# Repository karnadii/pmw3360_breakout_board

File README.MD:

# PMW3360 Minimal Breakout Board
my version of PMW3360 breakout board from https://github.com/jfedor2/pmw3360-breakout/, I have a little space to put the breakout in so that's why the shape is weird. only work for 3.3v, Not tested yet.

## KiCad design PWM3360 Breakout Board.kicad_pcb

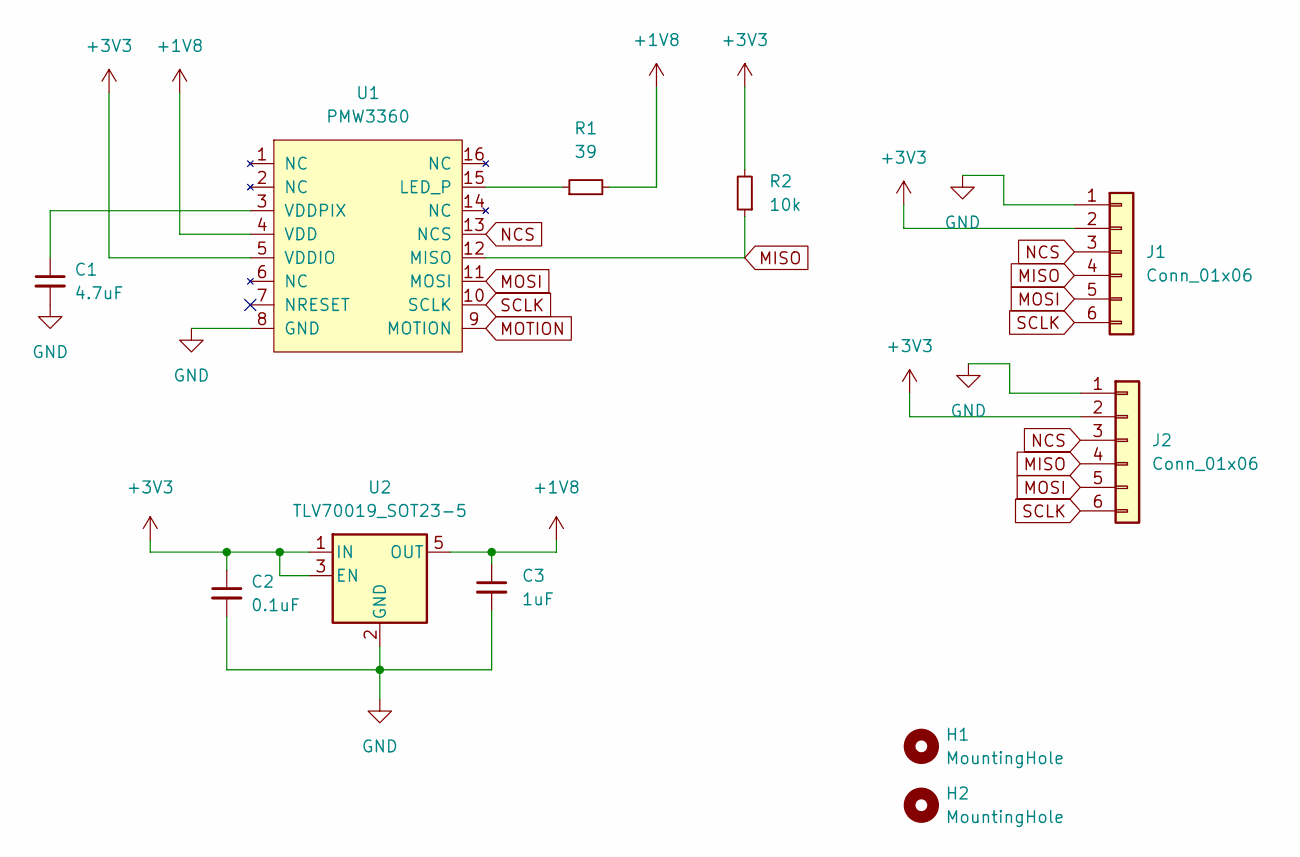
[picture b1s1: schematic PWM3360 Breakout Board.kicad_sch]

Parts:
C1: 4.7uF; C_0603_1608Metric_Pad1.08x0.95mm_HandSolder; LCSC C19666
C2: 0.1uF; C_0603_1608Metric_Pad1.08x0.95mm_HandSolder; LCSC C14663
C3: 1uF; C_0603_1608Metric_Pad1.08x0.95mm_HandSolder; LCSC C15849
H1, H2: MountingHole; MountingHole_2.2mm_M2_DIN965_Pad
J1: Conn_01x06; JST_SH_SM06B-SRSS-TB_1x06-1MP_P1.00mm_Horizontal
J2: Conn_01x06; PinHeader_1x06_P2.54mm_Vertical
R1: 39; R_0603_1608Metric_Pad0.98x0.95mm_HandSolder; LCSC C365424
R2: 10k; R_0603_1608Metric_Pad0.98x0.95mm_HandSolder; LCSC C25804
U1: PMW3360
U2: TLV70019_SOT23-5; SOT-23-5; LCSC C146366

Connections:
+1V8: C3.1, R1.2, U1.4 (VDD), U2.5 (OUT)
+3V3: C2.1, J1.2, J2.2, R2.2, U1.5 (VDDIO), U2.1 (IN), U2.3 (EN)
GND: C1.2, C2.2, C3.2, J1.1, J2.1, U1.8 (GND), U2.2 (GND)
MISO: J1.4, J2.4, R2.1, U1.12 (MISO)
MOSI: J1.5, J2.5, U1.11 (MOSI)
MOTION: U1.9 (MOTION)
NCS: J1.3, J2.3, U1.13 (NCS)
unnamed: C1.1, U1.3 (VDDPIX)
unnamed: R1.1, U1.15 (LED_P)
SCLK: J1.6, J2.6, U1.10 (SCLK)

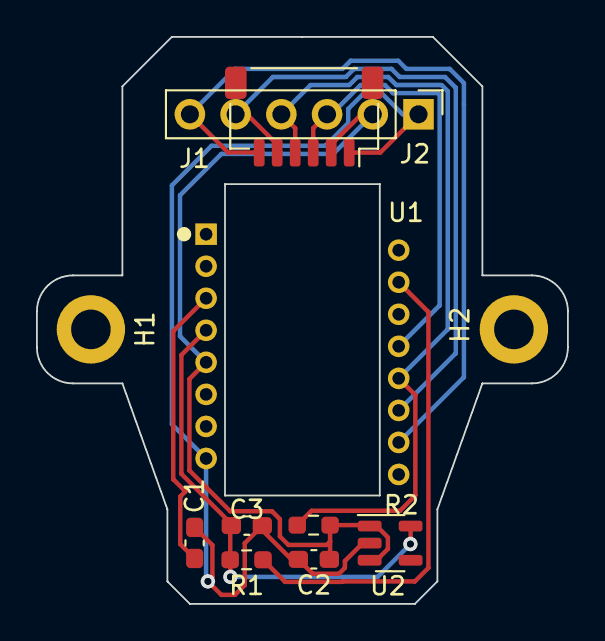
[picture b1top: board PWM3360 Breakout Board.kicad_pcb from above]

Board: 2 copper layers, 29.5 x 31.5 mm, 11 parts (0 on the bottom side), 9 nets.

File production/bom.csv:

Comment,Designator,Footprint,LCSC Part #
"4.7uF Unpolarized capacitor, small symbol",C1,C_0603_1608Metric_Pad1.08x0.95mm_HandSolder,C19666
"0.1uF Unpolarized capacitor, small symbol",C2,C_0603_1608Metric_Pad1.08x0.95mm_HandSolder,C14663
"1uF Unpolarized capacitor, small symbol",C3,C_0603_1608Metric_Pad1.08x0.95mm_HandSolder,C15849
MountingHole Mounting Hole without connection,"H1,H2",MountingHole_2.2mm_M2_DIN965_Pad,
"Conn_01x06 Generic connector, single row, 01x06, script generated (kicad-library-utils/schlib/autogen/connector/)",J1,JST_SH_SM06B-SRSS-TB_1x06-1MP_P1.00mm_Horizontal,
"Conn_01x06 Generic connector, single row, 01x06, script generated (kicad-library-utils/schlib/autogen/connector/)",J2,PinHeader_1x06_P2.54mm_Vertical,
"39 Resistor, small symbol",R1,R_0603_1608Metric_Pad0.98x0.95mm_HandSolder,C365424
"10k Resistor, small symbol",R2,R_0603_1608Metric_Pad0.98x0.95mm_HandSolder,C25804
PMW3360 ,U1,PMW3360,
"TLV70019_SOT23-5 200mA Low Dropout Voltage Regulator, Fixed Output 1.9V, SOT-23-5",U2,SOT-23-5,C146366

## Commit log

2022-08-13 make it more smaller
2022-08-13 add readme
2022-08-13 add spacing
